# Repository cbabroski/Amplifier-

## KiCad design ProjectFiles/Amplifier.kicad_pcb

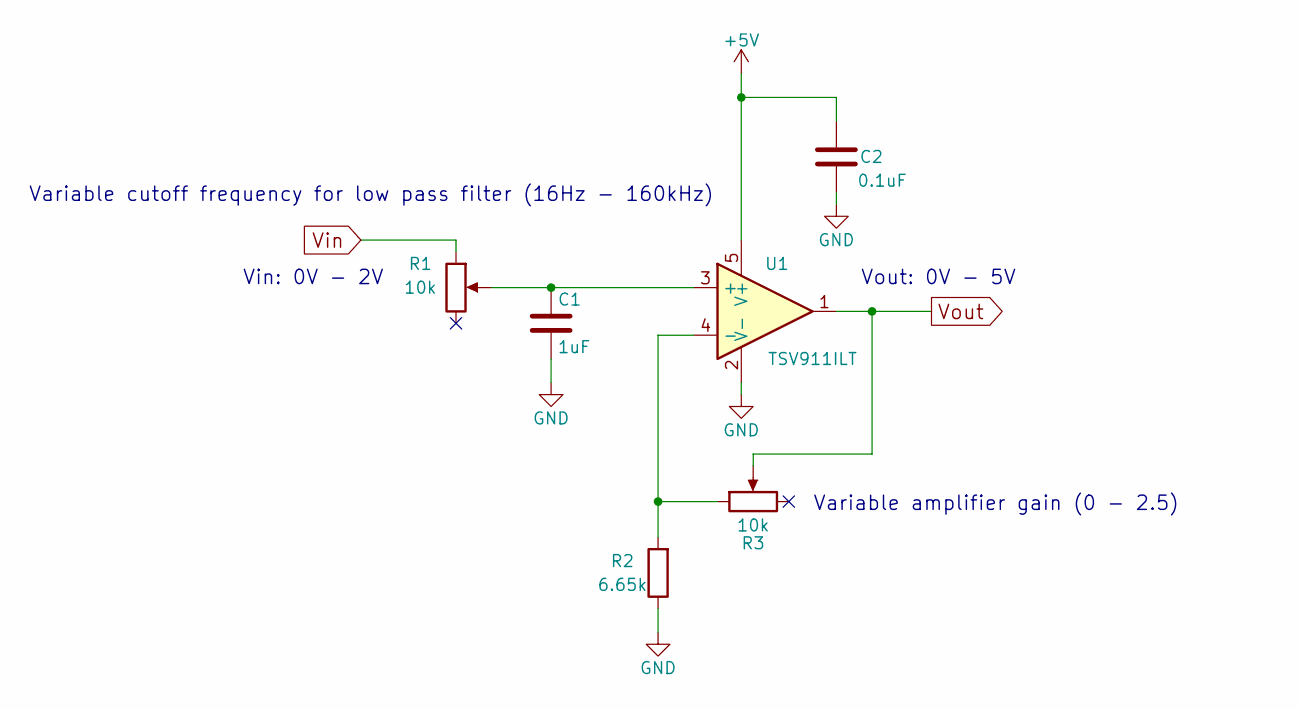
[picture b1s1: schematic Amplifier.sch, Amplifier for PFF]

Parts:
C1: 1uF; C_0805_HandSoldering; Voltage Rating 16V; Manufacturer Part Number CC0805KKX7R7BB105
C2: 0.1uF; C_0603_HandSoldering; Manufacturer Part Number CC0603KRX7R7BB104
R1, R3: 10k; 3310Y-001-103L; Manufacturer Part Number 3310Y-001-103L
R2: 6.65k; R_0805_HandSoldering; Manufacturer Part Number RC0805FR-076K65L
U1: TSV911ILT; SOT-23-5_HandSoldering; Manufacturer Part Number TSV911ILT

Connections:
+5V: C2.2, U1.5 (V+)
GND: C1.2, C2.1, R2.1, U1.2 (V-)
unnamed: C1.1, R1.2, U1.3 (+)
unnamed: R2.2, R3.1, U1.4 (-)
Vin: R1.1
Vout: R3.2, U1.1

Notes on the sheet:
Variable amplifier gain (0 - 2.5)
Variable cutoff frequency for low pass filter (16Hz - 160kHz)
Vin: 0V - 2V
Vout: 0V - 5V

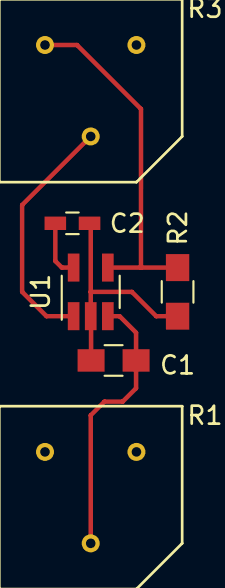
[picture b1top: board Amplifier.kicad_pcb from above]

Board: 2 copper layers, 6 parts (0 on the bottom side), 5 nets.

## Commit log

2017-03-07 PFF Amplifier Quiz Design
2017-03-07 Fixed pot footprints
2017-03-07 Removed unnecessary files
